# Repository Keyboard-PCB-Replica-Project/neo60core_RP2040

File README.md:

NEO60 CORE 레플리카 PCB입니다.

NEO60 CU에 체결이 되기는 하나, 실제 작동하는지는 확인하지 못했습니다.

추후에 확인해보겠습니다!

LED는 따로 부착해두지 않았습니다.

KT-0805W LED를 구입해서 LED 자리에 납땜해주시면 됩니다. 타오바오나 알리에서 같이 주문해주시면 되며,

납땜 난이도는 스위치보다도 못한 수준입니다.

물론 돈이 더 들어도 괜찮다면, LED까지 부착이 된 채로 배송 오는 옵션을 구현해두겠습니다.

추후에 추가될 수도 있습니다.

추가 필요 부품 : KT-0805W LED

작동 확인 여부 : O

----------------------------------------------------------

This is a replica PCB for the NEO60 CORE.

It fits the NEO60 CU, but I haven’t confirmed if it actually works yet.

I’ll test it later.

LEDs are not included.

You can buy KT-0805W LEDs and solder them yourself.

They’re easy to find on Taobao or AliExpress, and soldering them is even easier than switches.

If you're okay with a bit more cost, I might offer a version with the LEDs pre-installed.

It might be updated later.

Extra parts needed: KT-0805W LEDs

Tested and working: verified

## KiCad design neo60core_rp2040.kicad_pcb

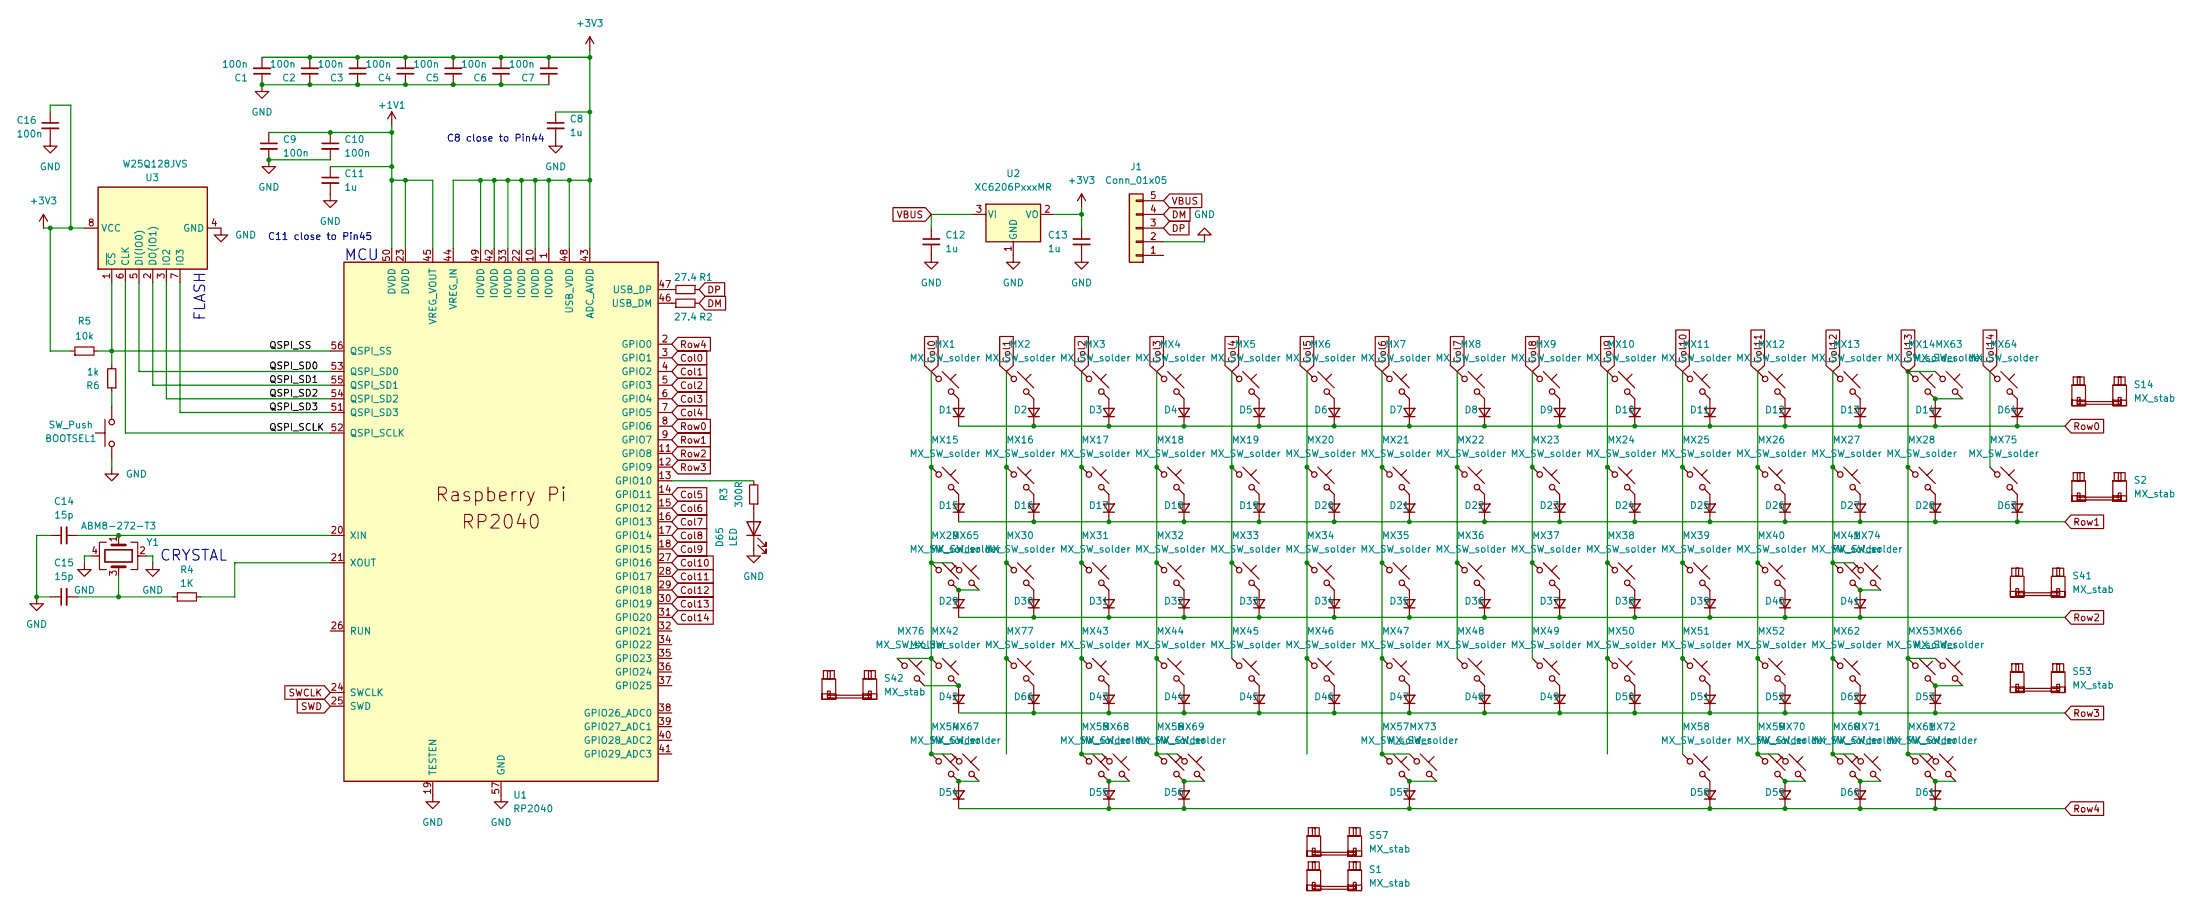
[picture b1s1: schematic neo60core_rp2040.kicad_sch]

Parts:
BOOTSEL1: SW_Push; SW_Push_1P1T_XKB_TS-1187A
C1, C2, C3, C4, C5, C6, C7, C9, C10, C16: 100n; C_0805_2012Metric
C8, C11, C12, C13: 1u; C_0805_2012Metric
C14, C15: 15p; C_0805_2012Metric
D1, D2, D3, D4, D5, D6, D7, D8, D9, D10, D11, D12, D13, D14, D15, D16, D17, D18, D19, D20, D21, D22, D23, D24, D25, D26, D27, D28, D29, D30, D31, D32, D33, D34, D35, D36, D37, D38, D39, D40, D41, D42, D43, D44, D45, D46, D47, D48, D49, D50, D51, D52, D53, D54, D55, D56, D57, D58, D59, D60, D61, D62, D63, D64, D66: D_Small; Diode_SOD-123_noref
D65: LED; KT-0805W
J1: Conn_01x05; pogo_2.54mm_1x5
MX1, MX2, MX3, MX4, MX5, MX6, MX7, MX8, MX9, MX10, MX11, MX12, MX13, MX14, MX15, MX16, MX17, MX18, MX19, MX20, MX21, MX22, MX23, MX24, MX25, MX26, MX27, MX28, MX29, MX30, MX31, MX32, MX33, MX34, MX35, MX36, MX37, MX38, MX39, MX40, MX41, MX42, MX43, MX44, MX45, MX46, MX47, MX48, MX49, MX50, MX51, MX52, MX53, MX54, MX55, MX56, MX57, MX58, MX59, MX60, MX61, MX62, MX63, MX64, MX65, MX66, MX67, MX68, MX69, MX70, MX71, MX72, MX73, MX74, MX75, MX76, MX77: MX_SW_solder; MX_PCB_1.00u_NoSilkscreen3
R1, R2: 27.4; R_0805_2012Metric
R3: 300R; R_0805_2012Metric
R4: 1K; R_0805_2012Metric
R5: 10k; R_0805_2012Metric
R6: 1k; R_0805_2012Metric
S1: MX_stab; Stabilizer_MX_7.00u
S2, S14, S41, S42, S53: MX_stab; Stabilizer_MX_2.00u
S57: MX_stab; Stabilizer_MX_6.25u
U1: RP2040; RP2040-QFN-56
U2: XC6206PxxxMR; SOT-23
U3: W25Q128JVS; SOIC-8_5.23x5.23mm_P1.27mm
Y1: ABM8-272-T3; Oscillator_SMD_EuroQuartz_XO32-4Pin_3.2x2.5mm

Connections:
+1V1: C9.1, C10.1, C11.1, U1.23 (DVDD), U1.45 (VREG_VOUT), U1.50 (DVDD)
+3V3: C1.2, C2.2, C3.2, C4.2, C5.2, C6.2, C7.2, C8.1, C13.1, C16.1, R5.1, U1.1 (IOVDD), U1.10 (IOVDD), U1.22 (IOVDD), U1.33 (IOVDD), U1.42 (IOVDD), U1.43 (ADC_AVDD), U1.44 (VREG_IN), U1.48 (USB_VDD), U1.49 (IOVDD), U2.2 (VO), U3.8 (VCC)
/QSPI_SCLK: U1.52 (QSPI_SCLK), U3.6 (CLK)
/QSPI_SD0: U1.53 (QSPI_SD0), U3.5 (DI(IO0))
/QSPI_SD1: U1.55 (QSPI_SD1), U3.2 (DO(IO1))
/QSPI_SD2: U1.54 (QSPI_SD2), U3.3 (IO2)
/QSPI_SD3: U1.51 (QSPI_SD3), U3.7 (IO3)
/QSPI_SS: R5.2, R6.2, U1.56 (QSPI_SS), U3.1 (~CS)
Col0: MX1.1, MX15.1, MX29.1, MX42.1, MX54.1, MX65.1, MX67.1, MX76.1, U1.3 (GPIO1)
Col1: MX2.1, MX16.1, MX30.1, MX77.1, U1.4 (GPIO2)
Col2: MX3.1, MX17.1, MX31.1, MX43.1, MX55.1, MX68.1, U1.5 (GPIO3)
Col3: MX4.1, MX18.1, MX32.1, MX44.1, MX56.1, MX69.1, U1.6 (GPIO4)
Col4: MX5.1, MX19.1, MX33.1, MX45.1, U1.7 (GPIO5)
Col5: MX6.1, MX20.1, MX34.1, MX46.1, U1.14 (GPIO11)
Col6: MX7.1, MX21.1, MX35.1, MX47.1, MX57.1, MX73.1, U1.15 (GPIO12)
Col7: MX8.1, MX22.1, MX36.1, MX48.1, U1.16 (GPIO13)
Col8: MX9.1, MX23.1, MX37.1, MX49.1, U1.17 (GPIO14)
Col9: MX10.1, MX24.1, MX38.1, MX50.1, U1.18 (GPIO15)
Col10: MX11.1, MX25.1, MX39.1, MX51.1, MX58.1, U1.27 (GPIO16)
Col11: MX12.1, MX26.1, MX40.1, MX52.1, MX59.1, MX70.1, U1.28 (GPIO17)
Col12: MX13.1, MX27.1, MX41.1, MX60.1, MX62.1, MX71.1, MX74.1, U1.29 (GPIO18)
Col13: MX14.1, MX28.1, MX53.1, MX61.1, MX63.1, MX66.1, MX72.1, U1.30 (GPIO19)
Col14: MX64.1, MX75.1, U1.31 (GPIO20)
DM: J1.4, R2.2
DP: J1.3, R1.1
GND: BOOTSEL1.1, C1.1, C2.1, C3.1, C4.1, C5.1, C6.1, C7.1, C8.2, C9.2, C10.2, C11.2, C12.2, C13.2, C14.1, C15.1, C16.2, D65.1 (K), J1.2, U1.19 (TESTEN), U1.57 (GND), U2.1 (GND), U3.4 (GND), Y1.2, Y1.4
unnamed: BOOTSEL1.2, R6.1
unnamed: C15.2, R4.1, Y1.3
unnamed: D1.2 (A), MX1.2
unnamed: D2.2 (A), MX2.2
unnamed: D3.2 (A), MX3.2
unnamed: D4.2 (A), MX4.2
unnamed: D5.2 (A), MX5.2
unnamed: D6.2 (A), MX6.2
unnamed: D7.2 (A), MX7.2
unnamed: D8.2 (A), MX8.2
unnamed: D9.2 (A), MX9.2
unnamed: D10.2 (A), MX10.2
unnamed: D11.2 (A), MX11.2
unnamed: D12.2 (A), MX12.2
unnamed: D13.2 (A), MX13.2
unnamed: D14.2 (A), MX14.2, MX63.2
unnamed: D15.2 (A), MX15.2
unnamed: D16.2 (A), MX16.2
unnamed: D17.2 (A), MX17.2
unnamed: D18.2 (A), MX18.2
unnamed: D19.2 (A), MX19.2
unnamed: D20.2 (A), MX20.2
unnamed: D21.2 (A), MX21.2
unnamed: D22.2 (A), MX22.2
unnamed: D23.2 (A), MX23.2
unnamed: D24.2 (A), MX24.2
unnamed: D25.2 (A), MX25.2
unnamed: D26.2 (A), MX26.2
unnamed: D27.2 (A), MX27.2
unnamed: D28.2 (A), MX28.2
unnamed: D29.2 (A), MX29.2, MX65.2
unnamed: D30.2 (A), MX30.2
unnamed: D31.2 (A), MX31.2
unnamed: D32.2 (A), MX32.2
unnamed: D33.2 (A), MX33.2
unnamed: D34.2 (A), MX34.2
unnamed: D35.2 (A), MX35.2
unnamed: D36.2 (A), MX36.2
unnamed: D37.2 (A), MX37.2
unnamed: D38.2 (A), MX38.2
unnamed: D39.2 (A), MX39.2
unnamed: D40.2 (A), MX40.2
unnamed: D41.2 (A), MX41.2, MX74.2
unnamed: D42.2 (A), MX42.2, MX76.2
unnamed: D43.2 (A), MX43.2
unnamed: D44.2 (A), MX44.2
unnamed: D45.2 (A), MX45.2
unnamed: D46.2 (A), MX46.2
unnamed: D47.2 (A), MX47.2
unnamed: D48.2 (A), MX48.2
unnamed: D49.2 (A), MX49.2
unnamed: D50.2 (A), MX50.2
unnamed: D51.2 (A), MX51.2
unnamed: D52.2 (A), MX52.2
unnamed: D53.2 (A), MX53.2, MX66.2
unnamed: D54.2 (A), MX54.2, MX67.2
unnamed: D55.2 (A), MX55.2, MX68.2
unnamed: D56.2 (A), MX56.2, MX69.2
unnamed: D57.2 (A), MX57.2, MX73.2
unnamed: D58.2 (A), MX58.2
unnamed: D59.2 (A), MX59.2, MX70.2
unnamed: D60.2 (A), MX60.2, MX71.2
unnamed: D61.2 (A), MX61.2, MX72.2
unnamed: D62.2 (A), MX62.2
unnamed: D63.2 (A), MX75.2
unnamed: D64.2 (A), MX64.2
unnamed: D65.2 (A), R3.1
unnamed: D66.2 (A), MX77.2
unnamed: R3.2, U1.13 (GPIO10)
unnamed: R2.1, U1.46 (USB_DM)
unnamed: R1.2, U1.47 (USB_DP)
unnamed: C14.2, U1.20 (XIN), Y1.1
unnamed: R4.2, U1.21 (XOUT)
Row0: D1.1 (K), D2.1 (K), D3.1 (K), D4.1 (K), D5.1 (K), D6.1 (K), D7.1 (K), D8.1 (K), D9.1 (K), D10.1 (K), D11.1 (K), D12.1 (K), D13.1 (K), D14.1 (K), D64.1 (K), U1.8 (GPIO6)
Row1: D15.1 (K), D16.1 (K), D17.1 (K), D18.1 (K), D19.1 (K), D20.1 (K), D21.1 (K), D22.1 (K), D23.1 (K), D24.1 (K), D25.1 (K), D26.1 (K), D27.1 (K), D28.1 (K), D63.1 (K), U1.9 (GPIO7)
Row2: D29.1 (K), D30.1 (K), D31.1 (K), D32.1 (K), D33.1 (K), D34.1 (K), D35.1 (K), D36.1 (K), D37.1 (K), D38.1 (K), D39.1 (K), D40.1 (K), D41.1 (K), U1.11 (GPIO8)
Row3: D42.1 (K), D43.1 (K), D44.1 (K), D45.1 (K), D46.1 (K), D47.1 (K), D48.1 (K), D49.1 (K), D50.1 (K), D51.1 (K), D52.1 (K), D53.1 (K), D62.1 (K), D66.1 (K), U1.12 (GPIO9)
Row4: D54.1 (K), D55.1 (K), D56.1 (K), D57.1 (K), D58.1 (K), D59.1 (K), D60.1 (K), D61.1 (K), U1.2 (GPIO0)
SWCLK: U1.24 (SWCLK)
SWD: U1.25 (SWD)
VBUS: C12.1, J1.5, U2.3 (VI)

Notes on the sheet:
C11 close to Pin45
MCU
CRYSTAL
C8 close to Pin44
FLASH

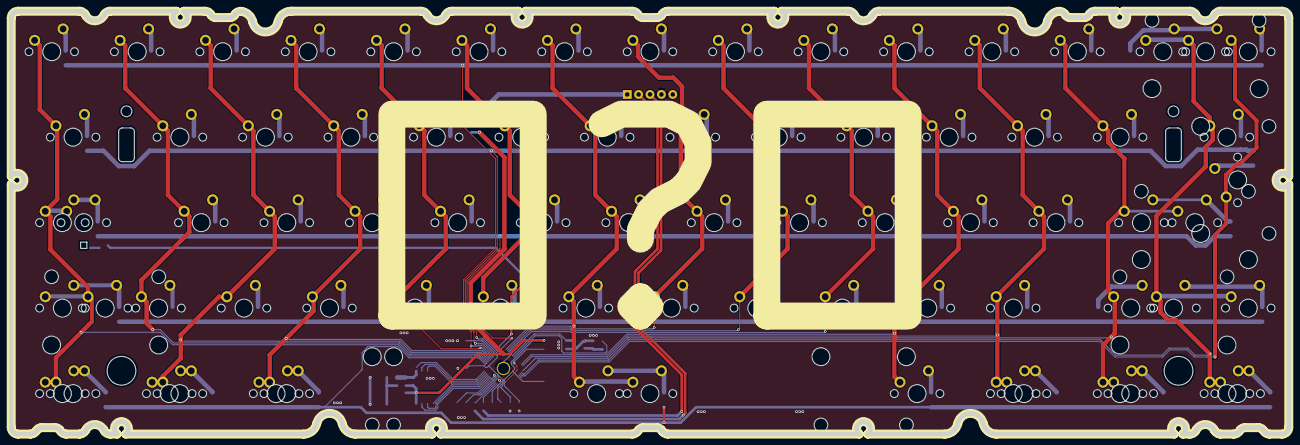
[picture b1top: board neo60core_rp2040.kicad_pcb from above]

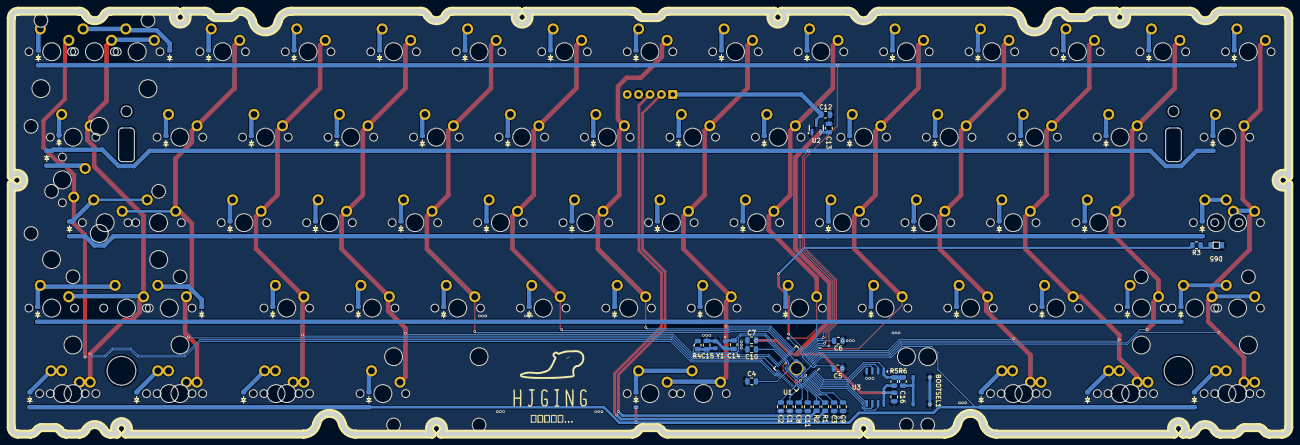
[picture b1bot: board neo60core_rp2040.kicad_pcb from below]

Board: 2 copper layers, 284.8 x 94.3 mm, 178 parts (93 on the bottom side), 105 nets.

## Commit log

2025-07-03 V1.0
2025-07-03 V1.1
2025-07-04 V1.2
2025-07-04 firmware update
